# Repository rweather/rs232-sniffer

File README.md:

RS-232 Sniffer Box
==================

This repository contains schematics, a PCB layout, and 3D-printable box
for a "RS-232 Sniffer" that my friend Chris asked me to design in 2019.

Chris needed a way to sniff the traffic between two serial devices,
and to get a visual indication as to which signals were active.

A little bit of mucking around in [KiCad](https://www.kicad.org/) and
[OpenSCAD](https://openscad.org/) and I had a design.  Chris later
improved on my original 3D-printable box design.

Multiple copies of the box have been made and have seen heavy use at
our workplace for monitoring serial communications; particularly for
SCADA systems.

The boxes have also proven useful to check if serial ports are working
at all, and to track down problems with RTS/CTS handshaking and the like.

## Capabilities

* Pass-through from one end of the box to the other for the main
serial communications path.
* Two extra serial ports for monitoring the RX and TX sides of the
communications.  Any bytes that are sent on that side are also sent
to the "sniffer" ports, for monitoring on a connected PC using a
terminal program like [PuTTY](https://www.putty.org/).
* Optional null modem connection to cross-over RX and TX.
* Red and green LED's to indicate which RS-232 lines have a high or
low signal on them.
* Probe points to monitor the RS-232 signals on an oscilloscope.

Note that this is a sniffer rather than a breakout box, so it isn't
possible to reroute the signals from one end to the other.  All serial
ports are assumed to use the standard IBM RS-232 DB9 arrangement.

## Schematics

The KiCad schematics are in the `schematics/RS232Sniffer` directory.
The PDF version can be found [here](schematics/RS232Sniffer/PDF/RS232Sniffer.pdf).

## Gerber Files

The Gerber files can be found in the `schematics/RS232Sniffer/Gerber` directory.

## Parts List

<table border="1">
<tr><td><b>Part</b></td><td><b>Quantity</b></td><td><b>Designators</b></td></td></tr>
<tr><td>PCB</td><td>1</td><td>N/A</td></tr>
<tr><td>3mm Red LED</td><td>8</td><td>D1,D3,D5,D7,D9,D11,D13,D15 (top row)</td></tr>
<tr><td>3mm Green LED</td><td>8</td><td>D2,D4,D6,D8,D10,D12,D14,D16 (bottom row)</td></tr>
<tr><td>DB9 female connector</td><td>4</td><td>J1,J2,J3,J5</td></tr>
<tr><td>DB9 male connector</td><td>1</td><td>J4</td></tr>
<tr><td>8-pin 2.54mm terminal header or socket</td><td>1</td><td>J6</td></tr>
<tr><td>2-pin 2.54mm terminal header or socket</td><td>1</td><td>J7</td></tr>
<tr><td>1.2k Resistor, either 1/4W or 1/2W</td><td>8</td><td>R1,R2,R3,R4,R5,R6,R7,R8</td></tr>
<tr><td>SPDT slide switch or 3-pin terminal header, 2.54mm pitch</td><td>1</td><td>SW1 (normally set to the "Thru" position)</td></tr>
</table>

Jaycar has the DB9 connectors as part codes PS-0806 (female) and
PP-0803 (male).

## 3D-Printable Box

* [STL file for the box](box/RS232SnifferBox.stl)
* [OpenSCAD file for the box](box/RS232SnifferBox.scad)

Use metal sheet screws to affix the PCB to the bottom of the box.
The mounting holes may need to be drilled out a little depending upon
the type of screws you are using.

A lid cut from transparent acrylic sheet completes the look.

## License

<p xmlns:cc="http://creativecommons.org/ns#" xmlns:dct="http://purl.org/dc/terms/"><span property="dct:title">RS-232 Sniffer</span> by <span property="cc:attributionName">Rhys Weatherley</span> is licensed under <a href="http://creativecommons.org/licenses/by-nc-sa/4.0/?ref=chooser-v1" target="_blank" rel="license noopener noreferrer" style="display:inline-block;">Attribution-NonCommercial-ShareAlike 4.0 International</a></p>

## Contact

For more information on this project, or to suggest improvements,
please contact the author Rhys Weatherley via
[email](mailto:rhys.weatherley@gmail.com).

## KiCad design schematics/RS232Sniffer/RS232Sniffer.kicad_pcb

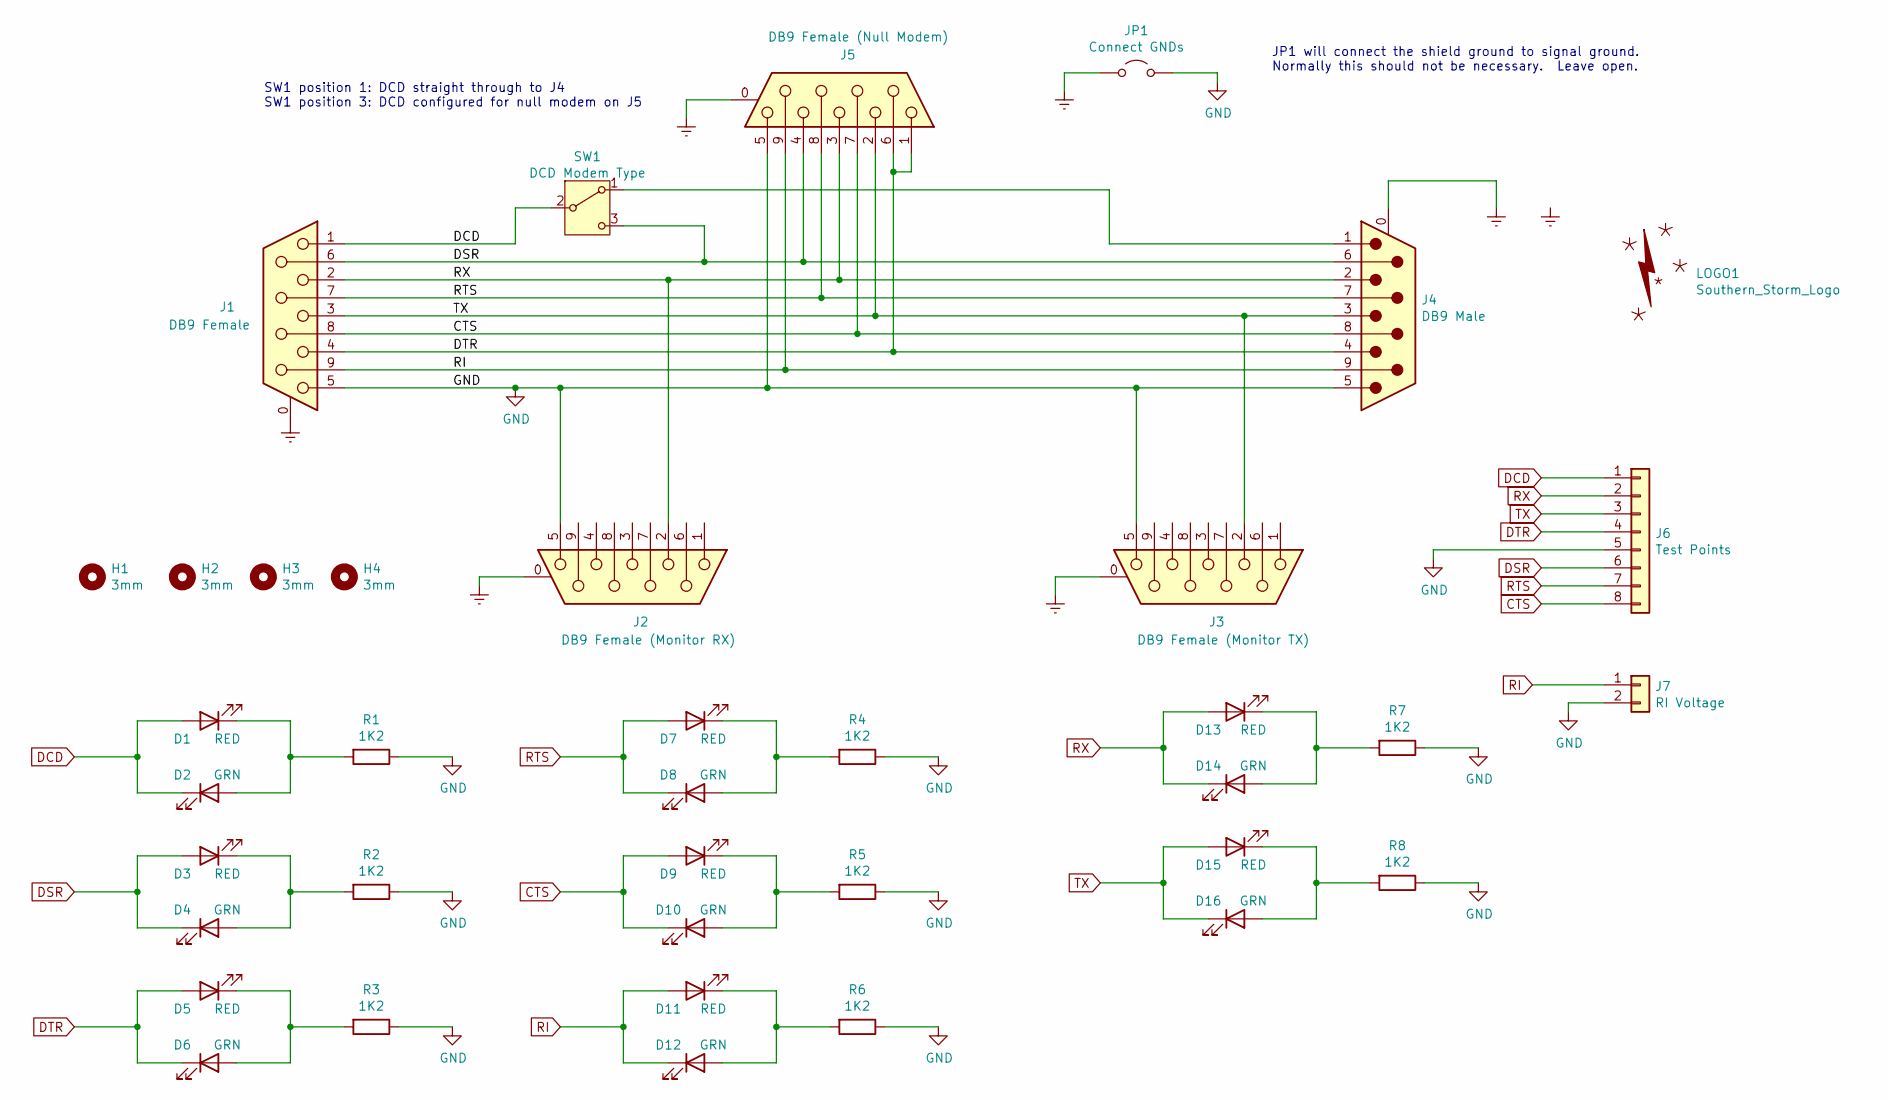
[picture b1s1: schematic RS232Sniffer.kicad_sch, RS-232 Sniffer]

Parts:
D1, D3, D5, D7, D9, D11, D13, D15: RED; LED_D3.0mm
D2, D4, D6, D8, D10, D12, D14, D16: GRN; LED_D3.0mm
H1, H2, H3, H4: 3mm; MountingHole_3mm
J1: DB9 Female; DSUB-9_Female_Horizontal_P2.77x2.84mm_EdgePinOffset4.94mm_H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
J2: DB9 Female (Monitor RX); DSUB-9_Female_Horizontal_P2.77x2.84mm_EdgePinOffset4.94mm_H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
J3: DB9 Female (Monitor TX); DSUB-9_Female_Horizontal_P2.77x2.84mm_EdgePinOffset4.94mm_H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
J4: DB9 Male; DSUB-9_Male_Horizontal_P2.77x2.84mm_EdgePinOffset4.94mm_Hou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
J5: DB9 Female (Null Modem); DSUB-9_Female_Horizontal_P2.77x2.84mm_EdgePinOffset4.94mm_H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
J6: Test Points; PinSocket_1x08_P2.54mm_Vertical
J7: RI Voltage; PinSocket_1x02_P2.54mm_Vertical
JP1: Connect GNDs; SolderJumper-2_P1.3mm_Open_RoundedPad1.0x1.5mm
LOGO1: Southern_Storm_Logo; Logo_Southern_Storm
R1, R2, R3, R4, R5, R6, R7, R8: 1K2; R_Axial_DIN0207_L6.3mm_D2.5mm_P10.16mm_Horizontal
SW1: DCD Modem Type; PinHeader_1x03_P2.54mm_Vertical

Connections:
CTS: D9.2 (A), D10.1 (K), J1.8, J4.8, J5.7, J6.8
DCD: D1.2 (A), D2.1 (K), J1.1, J6.1, SW1.2 (B)
DSR: D3.2 (A), D4.1 (K), J1.6, J4.6, J5.4, J6.6, SW1.3 (C)
DTR: D5.2 (A), D6.1 (K), J1.4, J4.4, J5.1, J5.6, J6.4
Earth: J1.0 (PAD), J2.0 (PAD), J3.0 (PAD), J4.0 (PAD), J5.0 (PAD), JP1.1 (A)
GND: J1.5, J2.5, J3.5, J4.5, J5.5, J6.5, J7.2, JP1.2 (B), R1.1, R2.1, R3.1, R4.1, R5.1, R6.1, R7.1, R8.1
unnamed: D1.1 (K), D2.2 (A), R1.2
unnamed: D3.1 (K), D4.2 (A), R2.2
unnamed: D5.1 (K), D6.2 (A), R3.2
unnamed: D7.1 (K), D8.2 (A), R4.2
unnamed: D9.1 (K), D10.2 (A), R5.2
unnamed: D11.1 (K), D12.2 (A), R6.2
unnamed: D13.1 (K), D14.2 (A), R7.2
unnamed: D15.1 (K), D16.2 (A), R8.2
unnamed: J4.1, SW1.1 (A)
RI: D11.2 (A), D12.1 (K), J1.9, J4.9, J5.9, J7.1
RTS: D7.2 (A), D8.1 (K), J1.7, J4.7, J5.8, J6.7
RX: D13.2 (A), D14.1 (K), J1.2, J2.2, J4.2, J5.3, J6.2
TX: D15.2 (A), D16.1 (K), J1.3, J3.2, J4.3, J5.2, J6.3

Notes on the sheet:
JP1 will connect the shield ground to signal ground. Normally this should not be necessary. Leave open.
SW1 position 1: DCD straight through to J4 SW1 position 3: DCD configured for null modem on J5

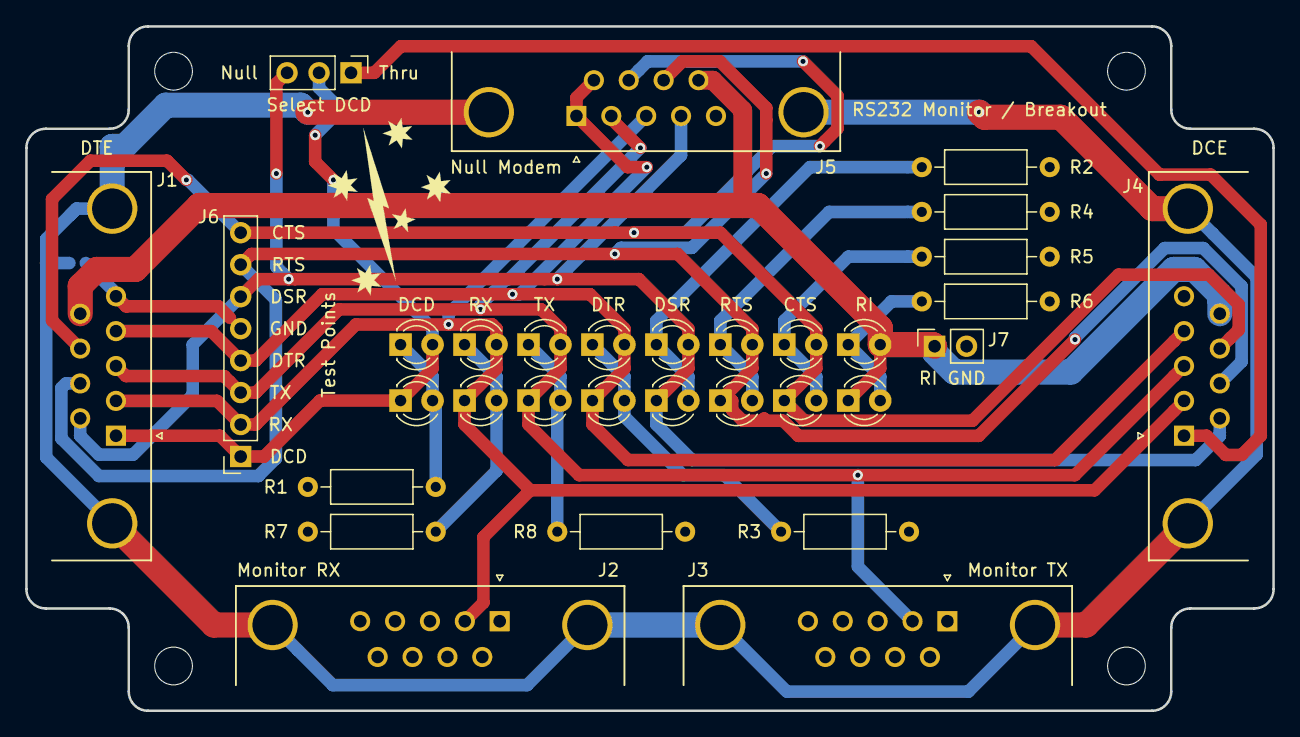
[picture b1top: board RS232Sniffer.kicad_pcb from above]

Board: 2 copper layers, 99.1 x 54.4 mm, 38 parts (1 on the bottom side), 19 nets.

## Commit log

2025-01-20 Check in the schematics and Gerber files
2025-01-21 Add a photo
2025-01-21 Add the 3D-printable box files
2025-01-21 Add the README and LICENSE
2025-01-21 Fix link to photo
